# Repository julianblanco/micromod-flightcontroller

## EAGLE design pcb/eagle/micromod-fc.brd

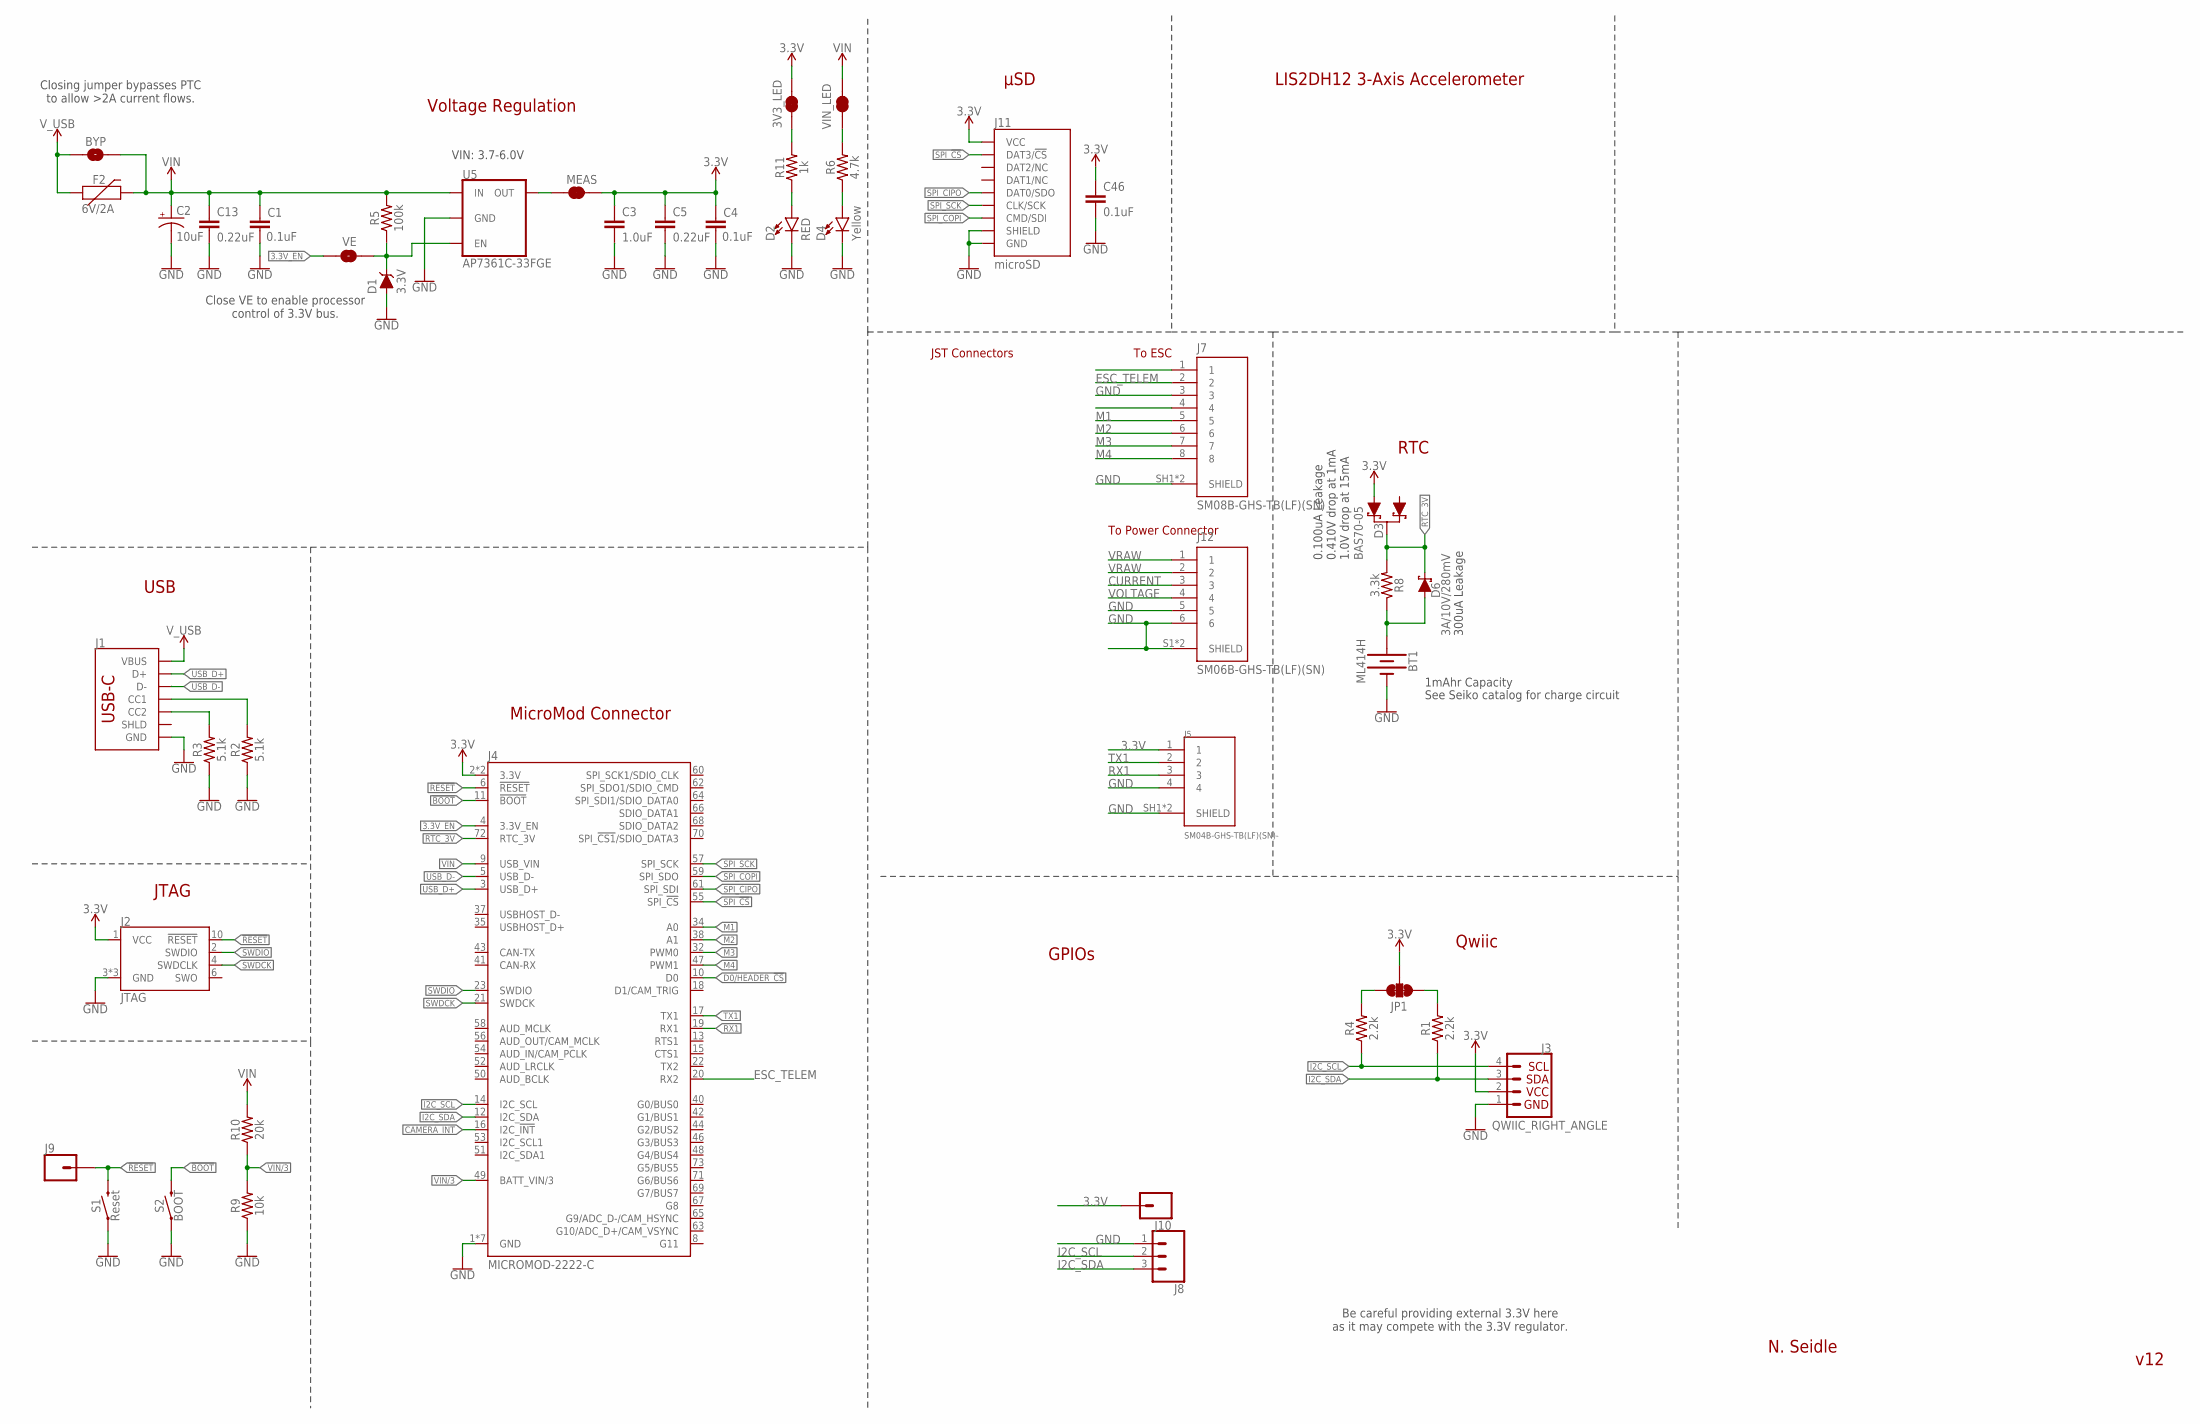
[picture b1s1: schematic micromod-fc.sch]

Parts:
3V3_LED: JUMPER-SMT_2_NC_TRACE_SILK; SMT-JUMPER_2_NC_TRACE_SILK
BT1: ML414H; ML414H_IV01E
BYP: JUMPER-SMT_2_NO_SILK; SMT-JUMPER_2_NO_SILK
C1, C4, C46: 0.1uF; 0603
C2: 10uF; EIA3216
C3: 1.0uF; 0603
C5, C13: 0.22uF; 0603
D1: 3.3V; SOD-323
D2: RED; LED-0603
D3: BAS70-05; SOT23-3
D4: Yellow; LED-0603
D6: 3A/10V/280mV; SOD-323
F2: 6V/2A; 1210
J1: USB_C_2-LAYER_PADS; USB-C-16P-2LAYER-PADS
J2: JTAG; 2X5-PTH-1.27MM
J3: QWIIC_RIGHT_ANGLE; JST04_1MM_RA
J4: MICROMOD-2222-C; M.2-CONNECTOR-E
J5: SM04B-GHS-TB(LF)(SN)-; JST_SM04B-GHS-TB(LF)(SN)-
J7: SM08B-GHS-TB(LF)(SN); JST_SM08B-GHS-TB(LF)(SN)
J8: CONN_03; 1X03
J9: CONN_01PTH_NO_SILK_YES_STOP; 1X01_NO_SILK
J10: CONN_01; 1X01
J11: microSD; MICRO-SD-SOCKET
J12: SM06B-GHS-TB(LF)(SN); JST_SM06B-GHS-TB(LF)(SN)
JP1: JUMPER-SMT_3_2-NC_TRACE_SILK; SMT-JUMPER_3_2-NC_TRACE_SILK
MEAS: JUMPER-COMBO_2_NC_TRACE; COMBO-JUMPER_2_NC_TRACE
R1, R4: 2.2k; 0603
R2, R3: 5.1k; 0603
R5: 100k; 0603
R6: 4.7k; 0603
R8: 3.3k; 0603
R9: 10k; 0603
R10: 20k; 0603
R11: 1k; 0603
S1: Reset; TACTILE_SWITCH_SMD_5.2MM
S2: BOOT; TACTILE_SWITCH_SMD_5.2MM
U5: AP7361C-33FGE; UDFN-8
VE: JUMPER-SMT_2_NO_SILK; SMT-JUMPER_2_NO_SILK
VIN_LED: JUMPER-SMT_2_NC_TRACE_SILK; SMT-JUMPER_2_NC_TRACE_SILK

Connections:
3.3V: 3V3_LED.2, C3.1, C4.1, C5.1, C46.1, D3.2 (A1), J2.1 (VCC), J3.2, J4.2 (3.3V), J4.74 (3.3V), J5.1, J10.1, J11.VCC, JP1.2, MEAS.2, MEAS.4 (2)
3.3V_EN: J4.4 (3.3V_EN), VE.1
!BOOT!: J4.11 (!BOOT!), S2.3 (2), S2.4 (2)
!RESET!: J2.10 (!RESET), J4.6 (!RESET!), J9.1, S1.3 (2), S1.4 (2)
CAMERA_INT: J4.16 (I2C_!INT!)
CURRENT: J12.3
D0/HEADER_!CS!: J4.10 (D0)
ESC_TELEM: J4.20 (RX2), J7.2
GND: BT1.-, C1.2, C2.-, C3.2, C4.2, C5.2, C13.2, C46.2, D1.A, D2.C, D4.C, J1.GND, J1.GND2 (GND), J2.3 (GND), J2.5 (GND), J2.9 (GND), J3.1, J4.1 (GND), J4.7 (GND), J4.33 (GND), J4.36 (GND), J4.39 (GND), J4.45 (GND), J4.75 (GND), J5.4, J5.SH1 (SHIELD), J5.SH2 (SHIELD), J7.3, J7.SH1 (SHIELD), J7.SH2 (SHIELD), J8.1, J11.CD1 (SHIELD), J11.GND, J11.GND1 (GND), J11.GND3 (GND), J12.5, J12.6, J12.S1 (SHIELD), J12.S2 (SHIELD), R2.1, R3.1, R9.1, S1.1, S1.2 (1), S2.1, S2.2 (1), U5.4 (GND), U5.EP (GND)
I2C_SCL: J3.4, J4.14 (I2C_SCL), J8.2, R4.1
I2C_SDA: J3.3, J4.12 (I2C_SDA), J8.3, R1.1
M1: J4.34 (A0), J7.5
M2: J4.38 (A1), J7.6
M3: J4.32 (PWM0), J7.7
M4: J4.47 (PWM1), J7.8
unnamed: R6.2, VIN_LED.1
unnamed: JP1.3, R4.2
unnamed: JP1.1, R1.2
unnamed: 3V3_LED.1, R11.2
unnamed: D2.A, R11.1
unnamed: D4.A, R6.1
unnamed: J1.A5 (CC1), R2.2
unnamed: J1.B5 (CC2), R3.2
unnamed: D1.C, R5.1, U5.5 (EN), VE.2
unnamed: BT1.+, D6.A, R8.1
RTC_3V: D3.3 (C), D6.C, J4.72 (RTC_3V), R8.2
RX1: J4.19 (RX1), J5.3
SPI_!CS!: J4.55 (SPI_!CS!), J11.CS/DAT3 (DAT3/!CS!)
SPI_CIPO: J4.61 (SPI_SDI), J11.DO/DAT0 (DAT0/SDO)
SPI_COPI: J4.59 (SPI_SDO), J11.DI/CMD (CMD/SDI)
SPI_SCK: J4.57 (SPI_SCK), J11.SCLK (CLK/SCK)
SWDCK: J2.4 (SWDCLK), J4.21 (SWDCK)
SWDIO: J2.2 (SWDIO), J4.23 (SWDIO)
TX1: J4.17 (TX1), J5.2
USB_D+: J1.A6 (D+), J1.B6 (D+), J4.3 (USB_D+)
USB_D-: J1.A7 (D-), J1.B7 (D-), J4.5 (USB_D-)
VIN: BYP.2, C1.1, C2.+, C13.1, F2.2, J4.9 (USB_VIN), R5.2, R10.2, U5.8 (IN), VIN_LED.2
VIN/3: J4.49 (BATT_VIN/3), R9.2, R10.1
VOLTAGE: J12.4
VRAW: J12.1, J12.2
VREG_3.3V: MEAS.1, MEAS.3 (1), U5.1 (OUT)
V_USB: BYP.1, F2.1, J1.VBUS1 (VBUS), J1.VBUS2 (VBUS)

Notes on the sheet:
LIS2DH12 3-Axis Accelerometer
μSD
300uA Leakage
See Seiko catalog for charge circuit
1mAhr Capacity
Closing jumper bypasses PTC to allow >2A current flows.
JTAG
USB
GPIOs
Qwiic
RTC
Voltage Regulation
MicroMod Connector
0.100uA Leakage 0.410V drop at 1mA 1.0V drop at 15mA
N. Seidle
v12
VIN: 3.7-6.0V
Be careful providing external 3.3V here as it may compete with the 3.3V regulator.
Close VE to enable processor control of 3.3V bus.
To ESC
To Power Connector
JST Connectors

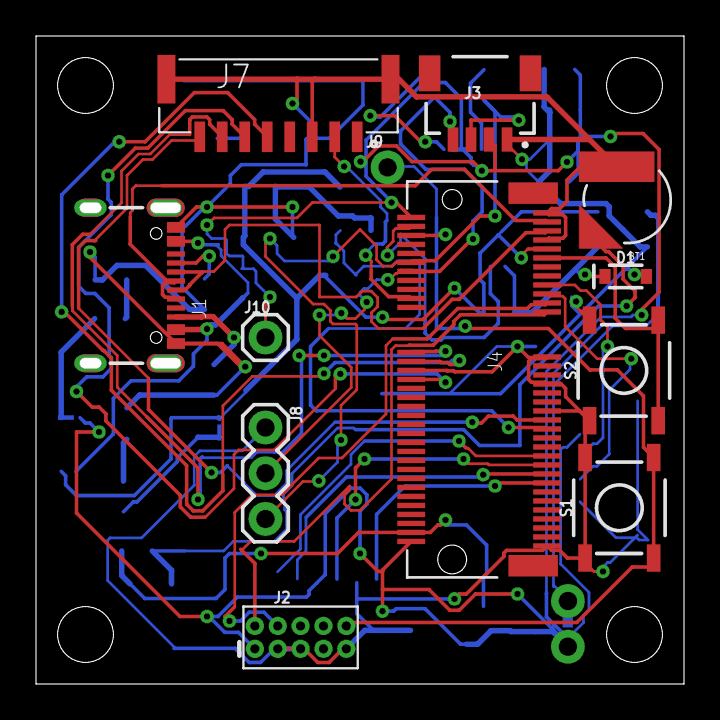
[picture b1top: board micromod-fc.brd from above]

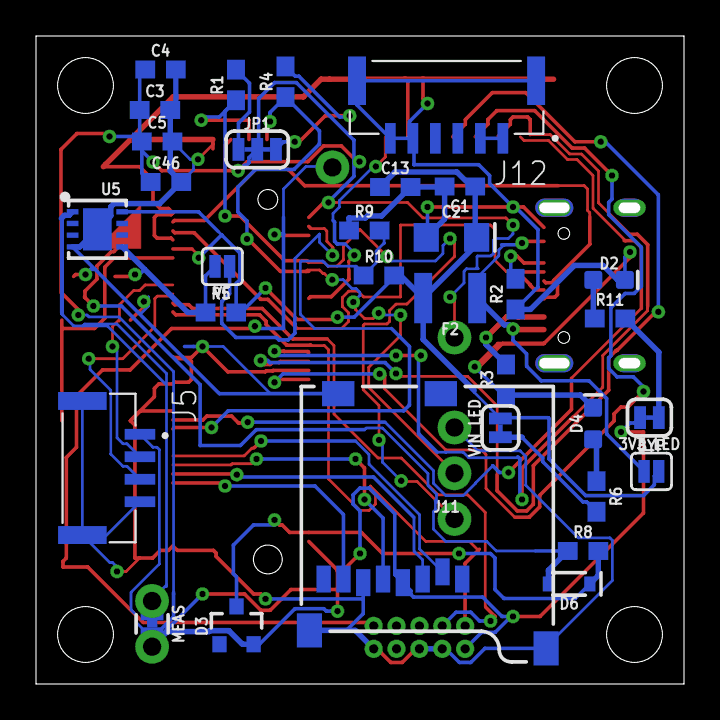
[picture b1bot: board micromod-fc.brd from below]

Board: 2 copper layers, 35.4 x 35.4 mm, 44 parts (32 on the bottom side), 38 nets.

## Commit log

2021-08-06 intial
2021-08-26 partial design
2021-08-26 i done messed up
2021-08-26 rev1
2021-08-26 rev1.1.
2021-08-27 maybe new

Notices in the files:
parts and their libraries:
SparkFun-Jumpers: Licensing: Creative Commons ShareAlike 4.0 International - https://creativecommons.org/licenses/by-sa/4.0
